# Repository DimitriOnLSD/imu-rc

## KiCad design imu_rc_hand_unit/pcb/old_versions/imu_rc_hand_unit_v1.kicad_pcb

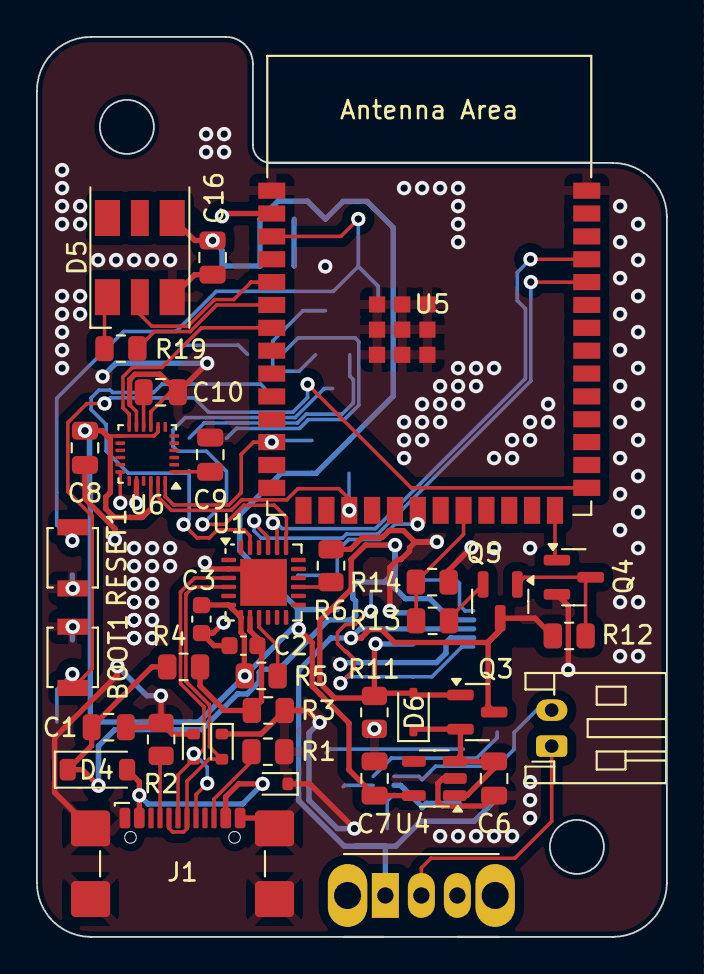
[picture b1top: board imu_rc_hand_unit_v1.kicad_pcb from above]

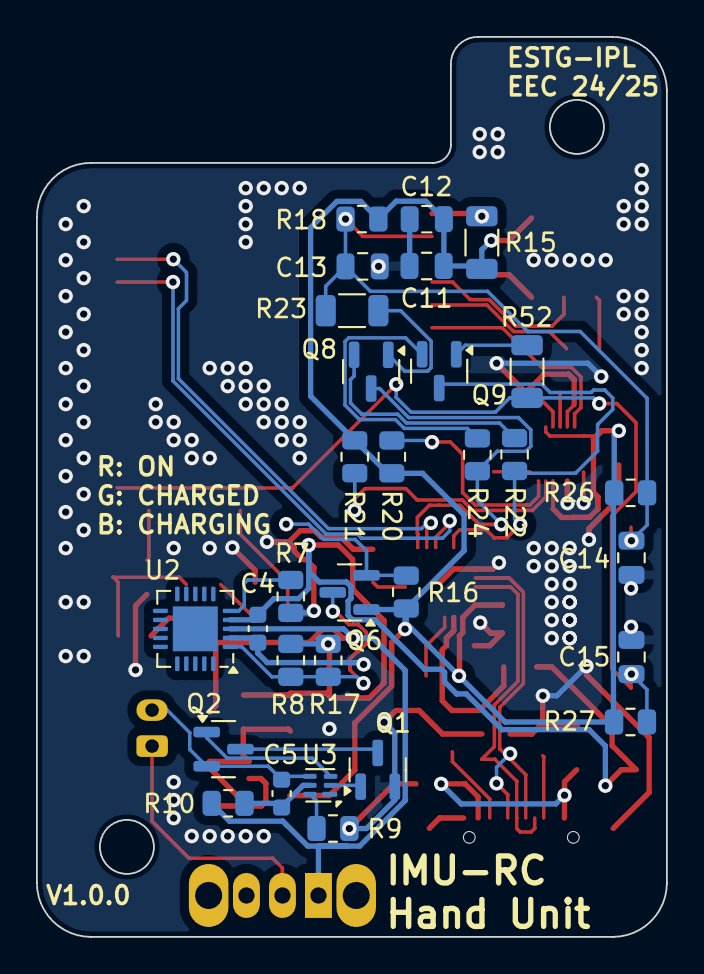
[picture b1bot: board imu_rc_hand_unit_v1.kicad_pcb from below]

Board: 2 copper layers, 35.0 x 50.0 mm, 68 parts (30 on the bottom side), 46 nets.

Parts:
BOOT1: B3U-1000P; SW_SPST_B3U-1000P
BT1: LiPo 3.7V 600mAh; JST_PH_S2B-PH-K_1x02_P2.00mm_Horizontal
C1: 10uF/16V; C_0805_2012Metric
C2, C4: 1uF/16V(10%); C_0603_1608Metric
C3: 10uF/25V; C_0603_1608Metric
C5: 0.1uF/16V; C_0603_1608Metric
C6, C7: 1uF/16V; C_0805_2012Metric
C8: 10nF/16V; C_0805_2012Metric
C9, C13: 1uF/16V(10%); C_0805_2012Metric
C10: 100nF/16V; C_0805_2012Metric
C11: 10uF/25V; C_0805_2012Metric
C12: 100nF/50V(10%); C_0805_2012Metric
C14, C15: 0.1uF/50V(10%); C_0805_2012Metric
C16: 1uF/50V(10%); C_0805_2012Metric
D1, D2, D3: LESD5D5.0CT1G; D_SOD-523
D4: 1N5819; D_SOD-123
D5: APA102; LED_Inolux_IN-P55TATRGB_PLCC6_5.0x5.5mm_P1.8mm
D6: BAT20J; D_SOD-323
J1: USB_C_Receptacle; USB_C_Receptacle_GCT_USB4110_MODIFIED
Q1, Q2, Q4: AO3400A; SOT-23
Q3, Q5: AO3401A; SOT-23
Q6: BSS138; SOT-23
Q8, Q9: 2N2907A; SOT-23
R1, R2: 5k1; R_0805_2012Metric
R3: 47k5; R_0805_2012Metric
R4: 22k1; R_0805_2012Metric
R5: 1k; R_0805_2012Metric
R6, R11, R12, R16, R17, R18, R22, R24, R26, R27: 10k; R_0805_2012Metric
R7, R8: 2k; R_0805_2012Metric
R9, R20, R21: 2k2; R_0805_2012Metric
R10: 330; R_0805_2012Metric
R13: 6k; R_0805_2012Metric
R14: 22k; R_0805_2012Metric
R15, R23, R52: 0; R_1206_3216Metric
R19: 470; R_0805_2012Metric
RESET1: B3U-1000P; SW_SPST_B3U-1000P
SW1: SW_SPDT; SW_Slide_SPDT_Angled_CK_OS102011MA1Q
U1: CP2102N; QFN-24-1EP_4x4mm_P0.5mm_EP2.6x2.6mm
U2: MCP73831; QFN-20-1EP_4x4mm_P0.5mm_EP2.5x2.5mm
U3: BQ297xy; WSON-6_1.5x1.5mm_P0.5mm
U4: AP2112K-3.3; SOT-23-5
U5: ESP32-S3-WROOM-1
U6: MPU-9250; InvenSense_QFN-24_3x3mm_P0.4mm_MODIFIED

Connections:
+3.3V: C3.2, C7.1, C8.1, C11.1, C12.1, C16.2, D5.4 (VCC), Q6.1 (G), R5.2, R15.1, R16.2, R18.2, R20.1, R21.2, R26.2, R27.2, U1.6 (VDD), U1.7 (VREGIN), U4.5 (VOUT), U6.8 (VDDIO), U6.13 (VDD), U6.22 (~CS)
+BATT: Q3.3 (D), Q5.3 (D), R10.2, R12.2, SW1.1 (A), U2.3 (V_{BAT})
BATT_READ: R13.2, R14.1, U5.22 (GPIO14/TOUCH14/ADC2_CH3/FSPIWP/FSPIDQS/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)
BATT_READ_EN: Q4.1 (G), U5.26 (GPIO45)
BOOT: BOOT1.2, C15.2, R27.1, R52.2, U5.27 (GPIO0/BOOT)
CHIP_PU: C13.1, C14.2, R18.1, R23.2, R26.1, RESET1.2, U5.3 (EN)
CHRG: Q6.2 (S), R16.1, U5.20 (GPIO12/TOUCH12/ADC2_CH1/FSPICLK/FSPIIO6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)
CHRG_5V: Q6.3 (D), R8.2, R17.1, U2.1 (STAT)
DTR: Q9.3 (E), R22.1, U1.23 (~DTR)
FUNCTION_LED_CLK: D5.2 (CI), U5.5 (GPIO5/TOUCH5/ADC1_CH4)
FUNCTION_LED_DATA: R19.2, U5.6 (GPIO6/TOUCH6/ADC1_CH5)
GND: BOOT1.1, C1.2, C2.2, C3.1, C4.2, C6.2, C7.2, C8.2, C9.1, C10.2, C11.2, C12.2, C13.2, C14.1, C15.1, C16.1, D1.1 (A1), D2.1 (A1), D3.1 (A1), D5.3 (GND), J1.A1 (GND), J1.A12 (GND), J1.B1 (GND), J1.B12 (GND), J1.S1 (SHIELD), Q1.2 (S), Q4.2 (S), R1.1, R2.1, R3.1, R6.2, R7.2, R9.1, R11.1, R14.2, RESET1.1, U1.2 (GND), U1.25 (GND), U2.2 (V_{SS}), U4.2 (GND), U5.1 (GND), U5.40 (GND), U5.41 (GND), U6.9 (AD0/MISO), U6.11 (FSYNC), U6.18 (GND), U6.20 (RESV_GND)
MPU_INT: U5.7 (GPIO7/TOUCH7/ADC1_CH6), U6.12 (INT)
unnamed: BT1.1 (+), SW1.2 (B)
unnamed: BT1.2 (-), C5.2, Q2.2 (S), U3.4 (VSS)
unnamed: D1.2 (A2), D4.2 (A), J1.A4 (VBUS), J1.A9 (VBUS), J1.B4 (VBUS), J1.B9 (VBUS)
unnamed: D2.2 (A2), J1.A7 (D-), J1.B7 (D-), U1.4 (D-)
unnamed: D3.2 (A2), J1.A6 (D+), J1.B6 (D+), U1.3 (D+)
unnamed: D5.1 (DI), R19.1
unnamed: C6.1, D6.1 (K), Q3.2 (S), U4.1 (VIN), U4.3 (EN)
unnamed: J1.A5 (CC1), R2.2
unnamed: J1.B5 (CC2), R1.2
unnamed: Q1.3 (D), Q2.3 (D)
unnamed: Q1.1 (G), U3.2 (Cout)
unnamed: Q2.1 (G), U3.3 (Dout)
unnamed: Q4.3 (D), Q5.1 (G), R12.1
unnamed: Q5.2 (S), R13.1
unnamed: Q8.2 (B), R22.2
unnamed: Q8.1 (C), R23.1
unnamed: Q9.2 (B), R24.2
unnamed: Q9.1 (C), R52.1
unnamed: C2.1, R3.2, R4.1, U1.8 (VBUS)
unnamed: R5.1, U1.9 (~RST)
unnamed: R6.1, U1.15 (~SUSPEND)
unnamed: R7.1, U2.5 (PROG)
unnamed: C5.1, R10.1, U3.5 (BAT)
unnamed: R9.2, U3.6 (V-)
unnamed: R15.2, U5.2 (3V3)
unnamed: C10.1, U6.10 (REGOUT)
unnamed: C9.2, U6.1 (RESV_VDDIO)
RTS: Q8.3 (E), R24.1, U1.19 (~RTS)
SCL: R21.1, U5.17 (GPIO9/TOUCH9/ADC1_CH8/FSPIHD/SUBSPIHD), U6.23 (SCL/SCLK)
SDA: R20.2, U5.12 (GPIO8/TOUCH8/ADC1_CH7/SUBSPICS1), U6.24 (SDA/MOSI)
U0RXD: U1.21 (TXD), U5.36 (U0RXD/GPIO44/CLK_OUT2)
U0TXD: U1.20 (RXD), U5.37 (U0TXD/GPIO43/CLK_OUT1)
VBUS: C1.1, C4.1, D4.1 (K), D6.2 (A), Q3.1 (G), R4.2, R8.1, R11.2, R17.2, U2.4 (V_{DD})
